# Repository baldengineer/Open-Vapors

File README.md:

# Open Vapors - Open Source Reflow Oven Controller

Additional Information on [baldengineer.com]( https://www.baldengineer.com/?s=open+vapors).

Key hardware pieces you'll need:
+ Toaster Oven with "Always On"
+ Custom controller board (or maybe an Arduino)
+ SSR (Recommend Crydom D2425)
+ 4-Line RGB LCD Display
+ 5 Button Keypad
+ 1 Push Button
+ Piezo Buzzer 

## /code
Contains all of the code for the menu display and reflow controller.

## /KiCad
The revision 2 board is a significant redesign from the first board. It integrates the shift register for the LCD and implements voltage rails to massively reduce internal wiring. Headers were also position to logical places on the PCB.

Buzzer is optional, but now implemented. USB connection through a 0.1" (2.54mm) header to a USB-port breakout. It is only intended for serial operation.

Recommend using ISP for programming. 

Also added port for AT-09 BLE module. (Not yet implemented)

## /enclosure
Laser cut enclosure. The top, bottom, and sides used 3mm black acrylic. The front and back panels are Black on White acrylic.

Originally designed in Autocad Inventor, student edition. Then exported to Adobe Illustrator (CS6 I think) files.

The bottom needs to be redesigned to get more support. ~~The SSR warps it over time.~~ After almost 5 years, it hasn't sagged anymore. I would still recommend a support around the SSR though.

## /original electronics - EAGLE
Rev 1 was created using an EAGLE. It worked okay, but relied on a "LCD Backpack" and was not an optimized design. (LEDs in the wrong place.) 

That said, it worked great for years.

The original keypad is in use still. Even though the debounce caps were totally wrong.

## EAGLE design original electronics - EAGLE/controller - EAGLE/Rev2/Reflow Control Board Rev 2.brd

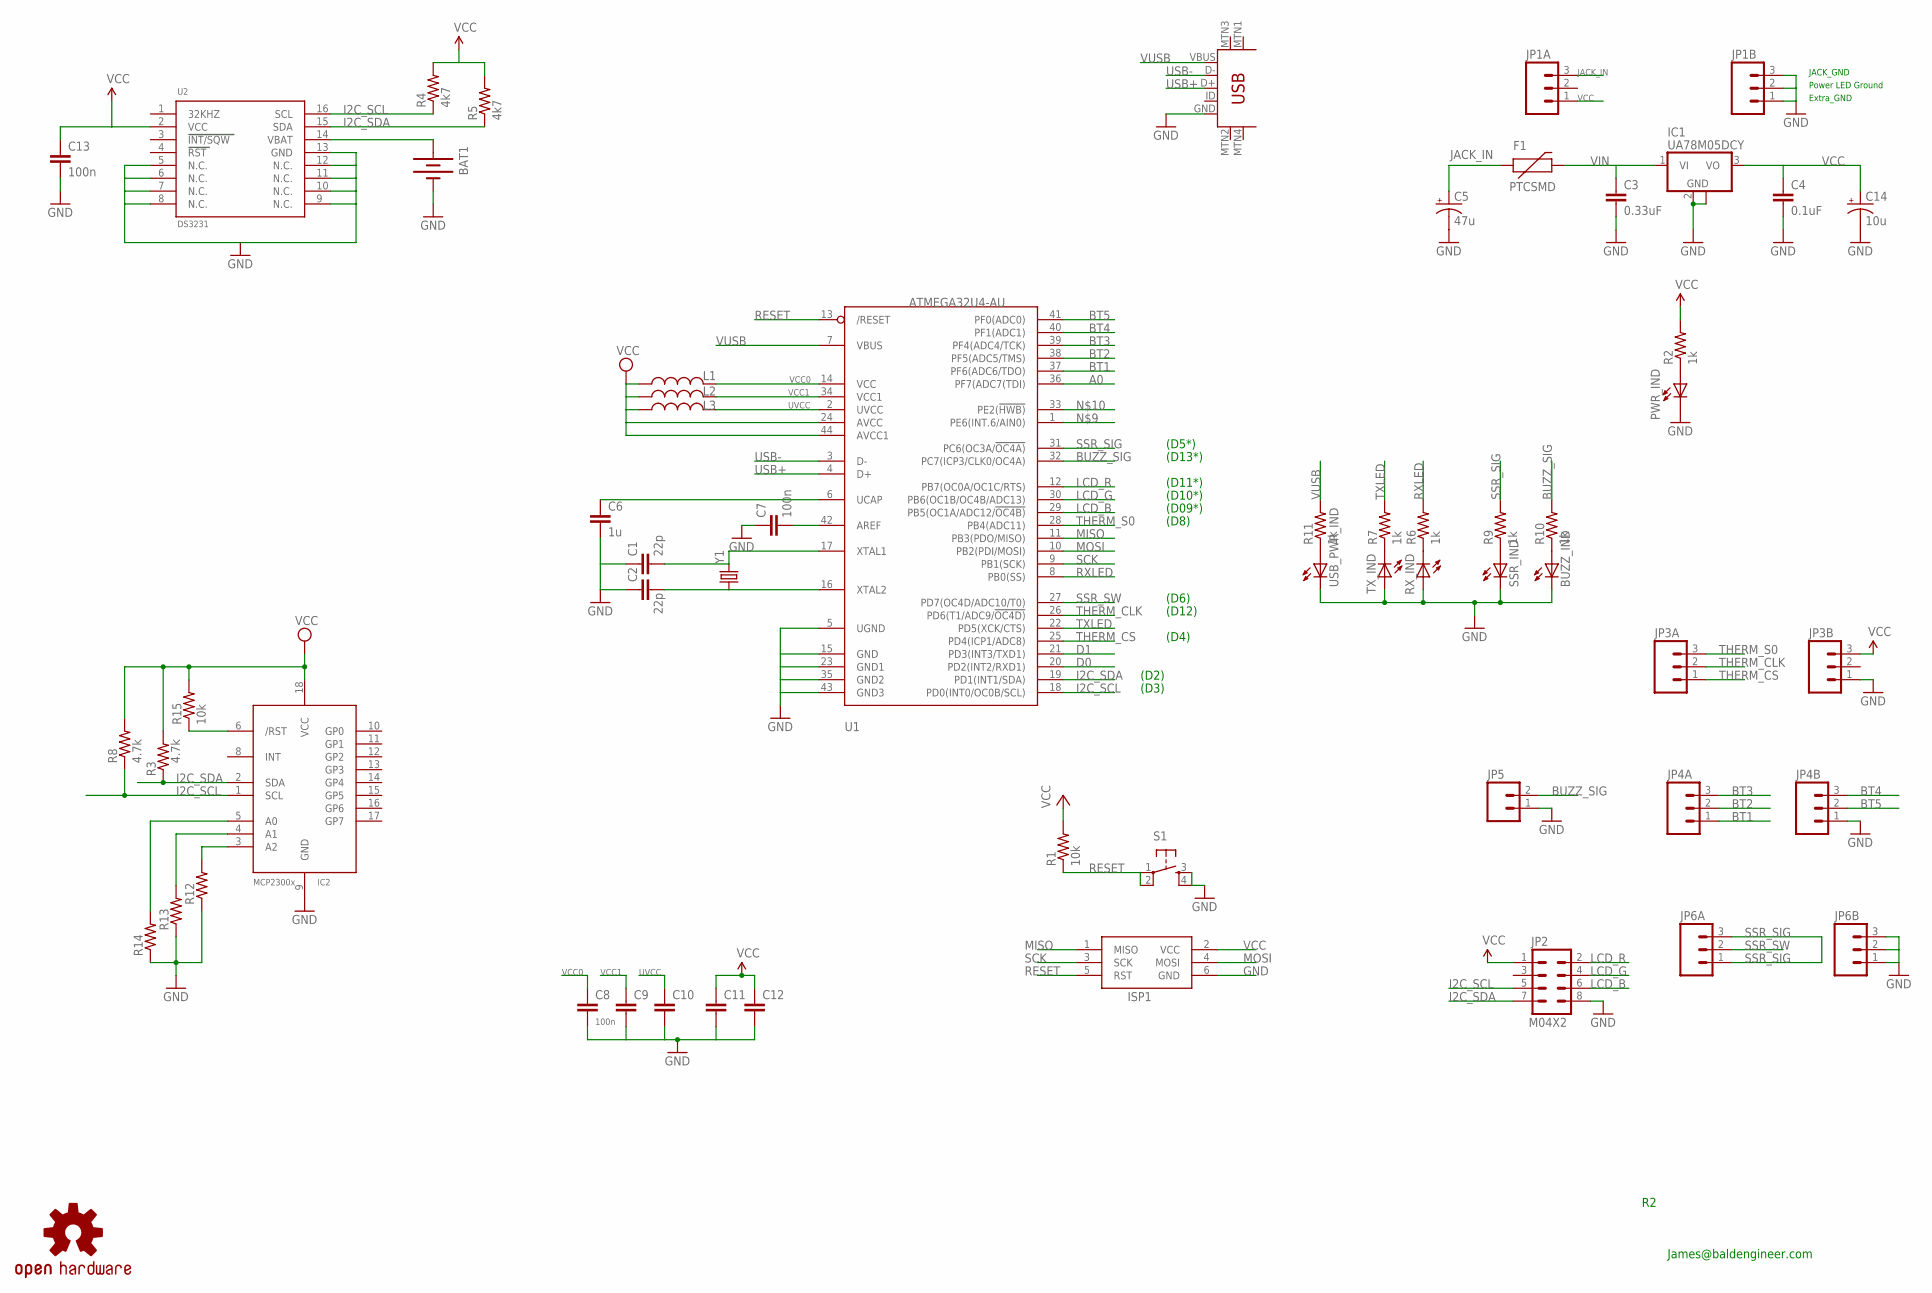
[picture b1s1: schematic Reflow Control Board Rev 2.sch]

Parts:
BAT1: BATTERY12MM; BATTCON_12MM
BUZZ_IND: LED1206; LED-1206
C1, C2: 22p; 1206
C3: 0.33uF; 1206
C4: 0.1uF; 1206
C5: 47u; D/7343-31R
C6: 1u; 1206
C7, C8, C9, C10, C11, C12, C13: 100n; 1206
C14: 10u; D/7343-31R
F1: PTCSMD; PTC-1206
IC1: UA78M05DCY; SOT223
IC2: MCP2300X/SO; SO18W
ISP1: AVRISP-6; AVRISP
JP1A, JP1B, JP3A, JP3B, JP4A, JP4B, JP6A, JP6B: M03LOCK; 1X03_LOCK
JP2: M04X2; 2X4
JP5: M02LOCK; 1X02_LOCK
L1, L2, L3: INDUCTOR0805; 0805
PWR_IND: LED1206; LED-1206
R1, R15: 10k; 1206
R2, R6, R7, R9, R10, R11: 1k; 1206
R3, R8: 4.7k; 1206
R4, R5: 4k7; 1206
R12, R13, R14: RESISTOR1206; 1206
RX_IND: LED1206; LED-1206
S1: TAC_SWITCHSMD; TACTILE_SWITCH_SMD
SSR_IND: LED1206; LED-1206
TX_IND: LED1206; LED-1206
U1: ATMEGA32U4-AU; TQFP44
U2: DS3231; SO16L
U$3: USB-MINIB-5PIN; USB-MINIB
U$4: OSHW-LOGOS; OSHW-LOGO-S
USB_PWR_IND: LED1206; LED-1206
Y1: CRYSTALHC49US; HC49US

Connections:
A0: U1.36 (PF7(ADC7(TDI))
BT1: JP4A.1, U1.37 (PF6(ADC6/TDO))
BT2: JP4A.2, U1.38 (PF5(ADC5/TMS))
BT3: JP4A.3, U1.39 (PF4(ADC4/TCK))
BT4: JP4B.3, U1.40 (PF1(ADC1))
BT5: JP4B.2, U1.41 (PF0(ADC0))
BUZZ_SIG: JP5.2, R10.2, U1.32 (PC7(ICP3/CLK0/OC4A))
D0: U1.20 (PD2(INT2/RXD1))
D1: U1.21 (PD3(INT3/TXD1))
GND: BAT1.GND (-), BUZZ_IND.C, C1.1, C2.1, C3.2, C4.2, C5.-, C6.2, C7.1, C8.2, C9.2, C10.2, C11.2, C12.2, C13.2, C14.-, IC1.2 (GND), IC1.4 (GND), IC2.9 (GND), ISP1.6 (GND), JP1B.1, JP1B.2, JP1B.3, JP2.8, JP3B.1, JP4B.1, JP5.1, JP6B.1, JP6B.2, JP6B.3, PWR_IND.C, R12.1, R13.1, R14.1, RX_IND.A, S1.3, S1.4, SSR_IND.C, TX_IND.A, U1.5 (UGND), U1.15 (GND), U1.23 (GND1), U1.35 (GND2), U1.43 (GND3), U2.5 (N.C.), U2.6 (N.C.), U2.7 (N.C.), U2.8 (N.C.), U2.9 (N.C.), U2.10 (N.C.), U2.11 (N.C.), U2.12 (N.C.), U2.13 (GND), U$3.GND, USB_PWR_IND.C
I2C_SCL: IC2.1 (SCL), JP2.5, R4.1, R8.1, U1.18 (PD0(INT0/OC0B/SCL)), U2.16 (SCL)
I2C_SDA: IC2.2 (SDA), JP2.7, R3.1, R5.1, U1.19 (PD1(INT1/SDA)), U2.15 (SDA)
JACK_IN: C5.+, F1.1, JP1A.3
LCD_B: JP2.6, U1.29 (PB5(OC1A/ADC12/!OC4B))
LCD_G: JP2.4, U1.30 (PB6(OC1B/OC4B/ADC13))
LCD_R: JP2.2, U1.12 (PB7(OC0A/OC1C/RTS))
MISO: ISP1.1 (MISO), U1.11 (PB3(PDO/MISO))
MOSI: ISP1.4 (MOSI), U1.10 (PB2(PDI/MOSI))
unnamed: C1.2, U1.17 (XTAL1), Y1.2
unnamed: C2.2, U1.16 (XTAL2), Y1.1
unnamed: R7.1, TX_IND.C
unnamed: C6.1, U1.6 (UCAP)
unnamed: C7.2, U1.42 (AREF)
unnamed: PWR_IND.A, R2.1
unnamed: R6.1, RX_IND.C
unnamed: R9.1, SSR_IND.A
unnamed: BAT1.PWR@2 (+), U2.14 (VBAT)
unnamed: IC2.3 (A2), R12.2
unnamed: BUZZ_IND.A, R10.1
unnamed: R11.1, USB_PWR_IND.A
unnamed: IC2.4 (A1), R13.2
unnamed: IC2.5 (A0), R14.2
unnamed: IC2.6 (/RST), R15.1
RESET: ISP1.5 (RST), R1.1, S1.1, S1.2, U1.13 (/RESET)
RXLED: R6.2, U1.8 (PB0(SS))
SCK: ISP1.3 (SCK), U1.9 (PB1(SCK))
SSR_SIG: JP6A.1, JP6A.3, R9.2, U1.31 (PC6(OC3A/!OC4A))
SSR_SW: JP6A.2, U1.27 (PD7(OC4D/ADC10/T0))
THERM_CLK: JP3A.2, U1.26 (PD6(T1/ADC9/!OC4D))
THERM_CS: JP3A.1, U1.25 (PD4(ICP1/ADC8))
THERM_S0: JP3A.3, U1.28 (PB4(ADC11))
TXLED: R7.2, U1.22 (PD5(XCK/CTS))
USB+: U1.4 (D+), U$3.D+
USB-: U1.3 (D-), U$3.D-
UVCC: C10.1, L3.2, U1.2 (UVCC)
VCC: C4.1, C11.1, C12.1, C13.1, C14.+, IC1.3 (VO), IC2.18 (VCC), ISP1.2 (VCC), JP1A.1, JP2.1, JP3B.3, L1.1, L2.1, L3.1, R1.2, R2.2, R3.2, R4.2, R5.2, R8.2, R15.2, U1.24 (AVCC), U1.44 (AVCC1), U2.2 (VCC)
VCC0: C8.1, L1.2, U1.14 (VCC)
VCC1: C9.1, L2.2, U1.34 (VCC1)
VIN: C3.1, F1.2, IC1.1 (VI)
VUSB: R11.2, U1.7 (VBUS), U$3.VBUS

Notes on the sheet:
Power LED Ground
JACK_GND
Extra_GND
(D2)
(D3)
(D4)
(D12)
(D8)
(D13*)
(D5*)
(D09*)
(D10*)
(D11*)
(D6)
James@baldengineer.com

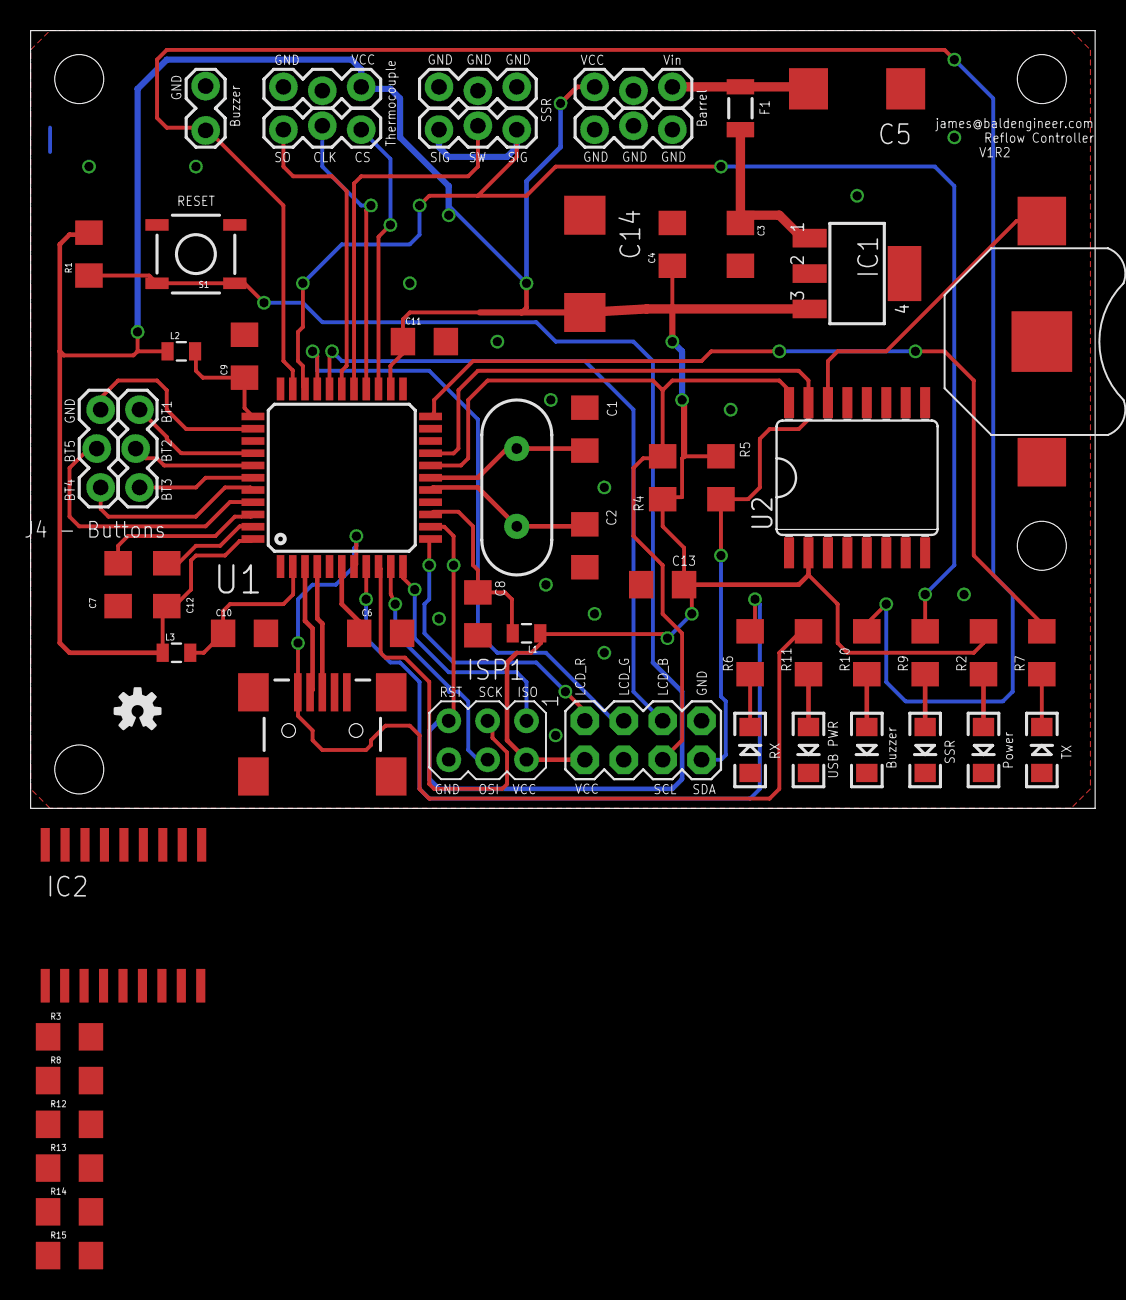
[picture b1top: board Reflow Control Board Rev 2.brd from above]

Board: 2 copper layers, 69.5 x 50.8 mm, 59 parts (0 on the bottom side), 47 nets.

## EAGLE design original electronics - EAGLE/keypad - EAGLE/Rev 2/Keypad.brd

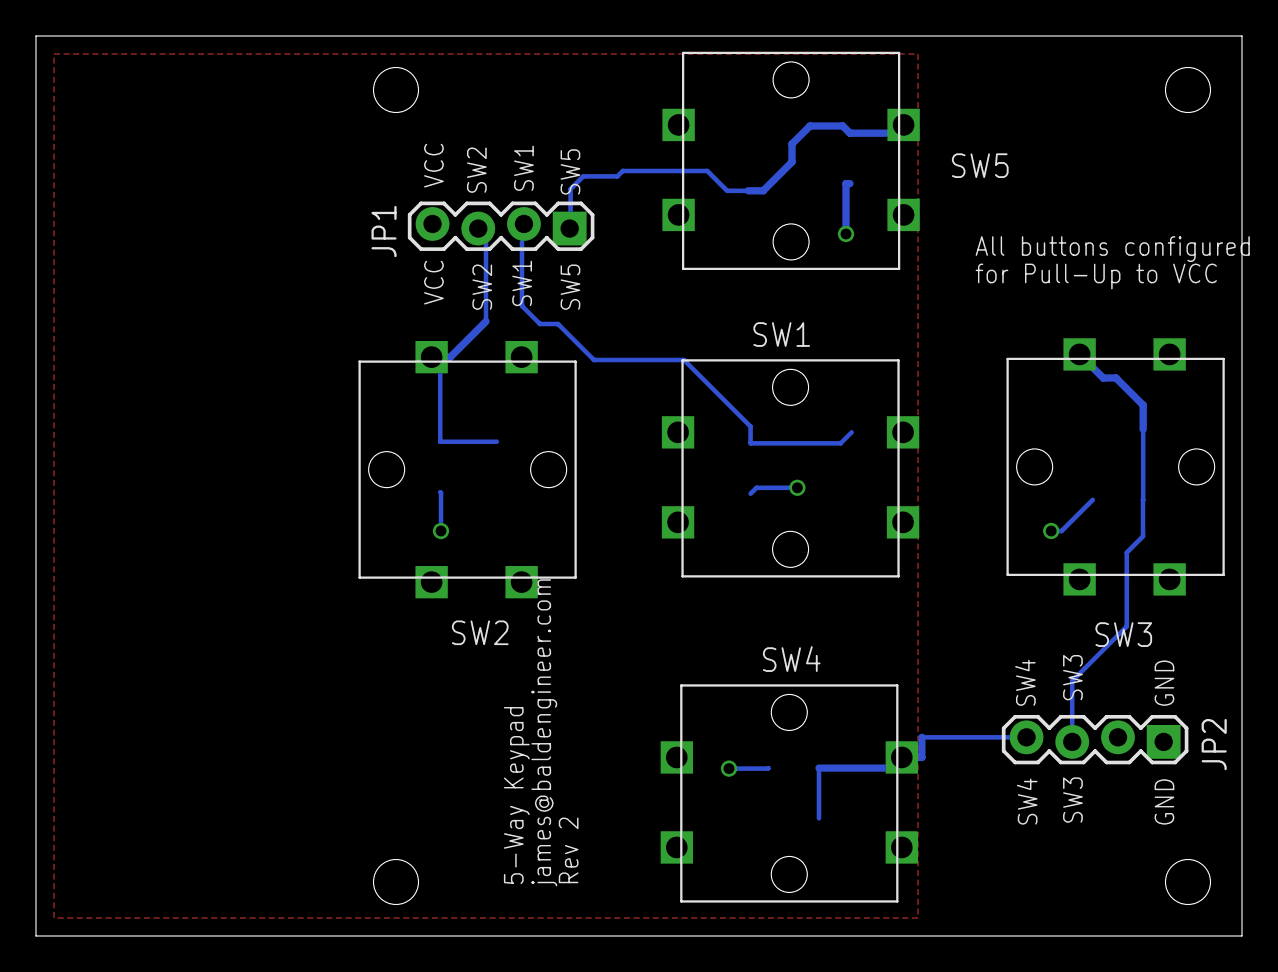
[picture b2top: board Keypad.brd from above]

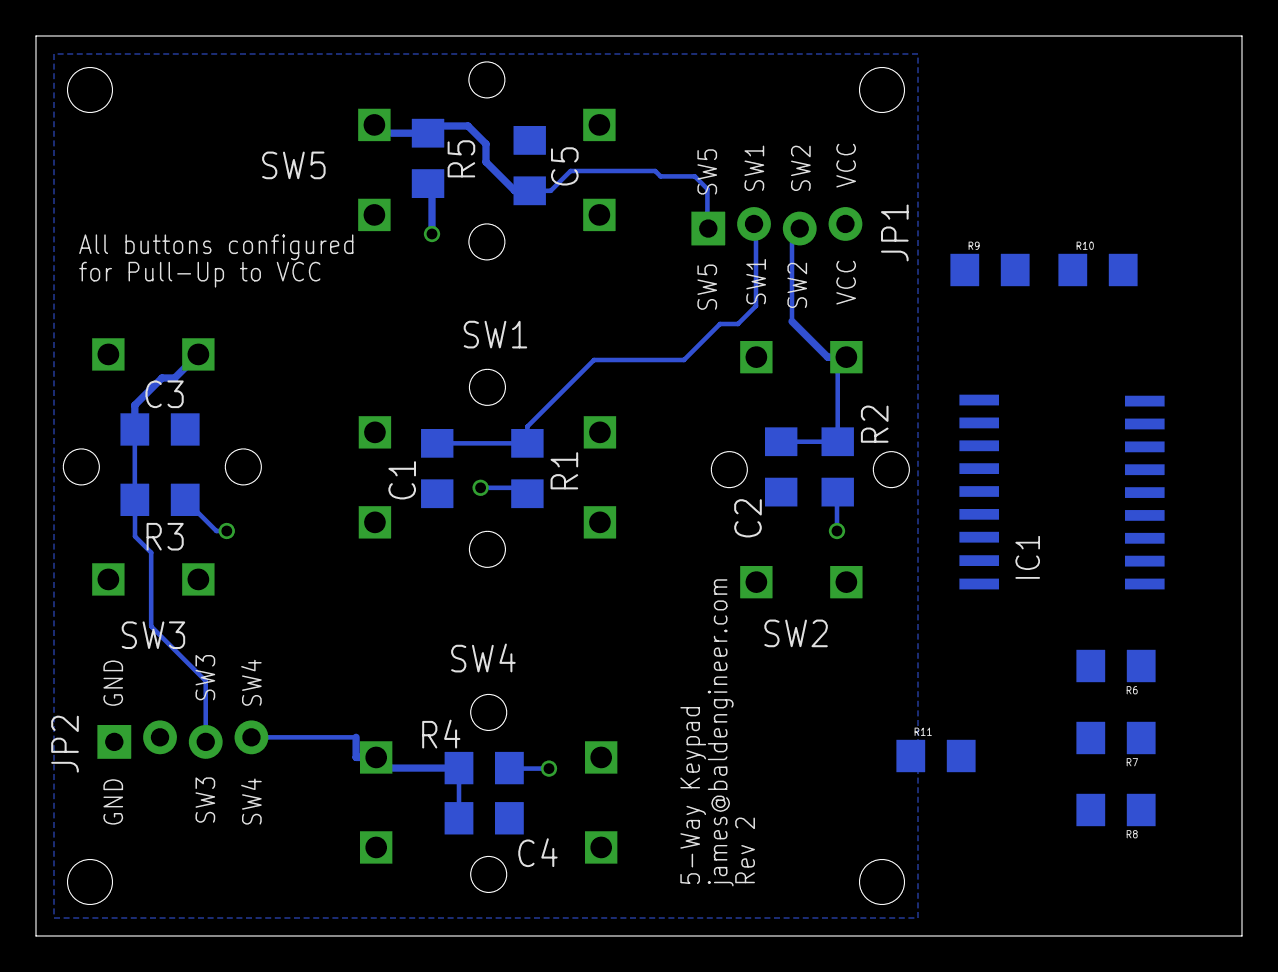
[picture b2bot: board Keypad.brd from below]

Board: 2 copper layers, 67.0 x 50.0 mm, 24 parts (17 on the bottom side), 13 nets.

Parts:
C1, C2, C3, C4, C5: 1206
IC1: MCP2300X/SO; SO18W
JP1, JP2: 1X04_LOCK
R1, R2, R3, R4, R5: 1206
R6, R7: 4.7k; 1206
R8: 10k; 1206
R9, R10, R11: 1k; 1206
SW1, SW2, SW3, SW4, SW5: TAC_PTH_12MM; TACTILE-PTH-12MM

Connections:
BT1: C1.1, JP1.2, R1.1, SW1.P$3
BT2: C2.1, JP1.3, R2.1, SW2.P$3
BT3: C3.1, JP2.3, R3.1, SW3.P$3
BT4: C4.1, JP2.4, R4.1, SW4.P$3
BT5: C5.1, JP1.1, R5.1, SW5.P$3
GND: C1.2, C2.2, C3.2, C4.2, C5.2, IC1.9, JP2.1, R9.1, R10.1, R11.1, SW1.P$2, SW1.P$4, SW2.P$2, SW2.P$4, SW3.P$2, SW3.P$4, SW4.P$2, SW4.P$4, SW5.P$2, SW5.P$4
unnamed: IC1.2, R7.1
unnamed: IC1.1, R6.1
unnamed: IC1.6, R8.1
unnamed: IC1.3, R9.2
unnamed: IC1.4, R10.2
unnamed: IC1.5, R11.2
VCC: IC1.18, JP1.4, R1.2, R2.2, R3.2, R4.2, R5.2, R6.2, R7.2, R8.2

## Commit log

2017-04-26 adding readme
2021-09-15 overdue commit, prepping for v2 update
2021-09-15 added MIT license
2021-09-15 archiving original control board created in EAGLE
2021-09-15 rev board converted from EAGLE to KiCad
2021-09-15 big big v2 code update
2021-09-15 updated readme to reflect v2 notes
2021-09-25 initial BLE support reporting current temperature
2021-09-29 change the soak state to accomodate proper soaking. also changed thermal timeout to be absolute value to account for if the temperature drops.
2021-09-29 fixed soak stage bug, fix manual SSR control, added max temperature check
2022-02-08 adding image
2022-02-08 added 3d render image, because pretty
2022-02-08 Added PDF of the schematic.

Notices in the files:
parts and their libraries:
SparkFun: Licensing: CC v3.0 Share-Alike You are welcome to use this library for commercial purposes.
